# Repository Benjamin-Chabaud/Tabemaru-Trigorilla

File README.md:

# Tabemaru Control Board

## Overview
This repository contains the firmware (`tabemaru-V5-verbose.ino`) and documentation for the **Tabemaru Control Board**. The system is built around an Arduino Mega 2560 architecture (specifically using an Anycubic Trigorilla motherboard) combined with a custom PCB.

The system is designed to automate a sequence involving valves, a motor, and a heated bed, while continuously logging environmental data (temperature and humidity) to both a Serial Monitor and an SD Card in a non-blocking manner.

## Firmware Logic Explanation
The firmware is built using a non-blocking architecture, utilizing `millis()` to manage multiple tasks simultaneously without halting the processor. 

### 1. The Operational Sequence
The core logic of the machine relies on a 4-step state machine triggered by a hardware button (Button X-).
*   **Step 1 (Valve 1):** The sequence begins, the hotbed turns on, and Valve 1 opens for `1m 40s`.
*   **Step 2 (Motor):** Valve 1 closes, and the Motor runs for `5s`.
*   **Step 3 (Valve 2):** The motor stops, and Valve 2 opens for `2m 20s`.
*   **Step 4 (Wait & Hotbed):** Valve 2 closes. The system waits until the total elapsed time reaches `800s`. During this entire 800-second sequence, the heated bed actively regulates its temperature. Once 800 seconds pass, the sequence automatically terminates and resets.

*Note: All timings are defined as constants at the top of the code and can be easily modified.*

### 2. Hardware Interrupts
To ensure zero-latency responsiveness, the physical buttons do not use standard `digitalRead()` polling. Instead, they use Hardware Interrupts (`attachInterrupt`). 
*   **X- Button (Sequence Start/Stop):** Reacts instantly to start the sequence or act as an emergency stop.
*   **Z- Button (LED / SD Eject):** A short press toggles the internal LED. Holding the button for 1.5 seconds safely ejects the SD card (suspends writing) or remounts it.

### 3. SD Card & Data Storage
The system logs data in CSV format. It features a robust **Hot-Swap background task**. If the SD card is removed (or communication fails due to interference), the system will safely catch the error and attempt to re-initialize the SD card every 10 seconds. When the card is reinserted, data logging resumes automatically.

**SD Card Requirements & Formatting:**
For the SD card module to work reliably with the Arduino architecture, the following requirements MUST be met:
*   **Capacity:** 8GB is highly recommended for maximum stability (though up to 32GB SDHC is technically supported). SDXC cards (64GB+) will not work.
*   **File System:** The card MUST be formatted in **FAT32** (or FAT16). exFAT, NTFS, or APFS are not supported by the standard Arduino library.
*   **Formatting Tool & Deep Reset:** It is strongly advised to use the official SD Association's *SD Memory Card Formatter*. If the Arduino fails to initialize the card, a standard "Quick Format" is often not enough. You must select **"Overwrite Format"** (Full Format) to completely wipe the flash memory sectors and rebuild the file system from scratch.
*   **Partition Scheme:** The card's partition map MUST be **MBR (Master Boot Record)**. If the card was previously formatted on a Mac or newer OS as GPT (GUID Partition Table), the Arduino will fail to read it. To fix this, the partition table must be completely wiped (e.g., using `diskpart > clean` on Windows) before reformatting to FAT32.
*   **File Naming:** The system writes to `LOG.CSV`, strictly adhering to the legacy 8.3 filename convention.

**Data Storage Capacity & Retention:**
At the current logging rate (one entry every 2 seconds), the system generates approximately 1.2 GB of CSV data per year of continuous 24/7 operation. An 8GB SD card (the recommended maximum size for optimal compatibility) can hold data for **over 5 years** before running out of space. 

Depending on your operational needs, you can either:
*   Safely eject the SD card every few years to manually archive and delete the data.
*   Modify the logging function in the firmware to implement a rolling log (automatically deleting the oldest data when space runs out).

**Hardware & Operational Recommendations:**
*   **Logic Level Shifting:** The Arduino outputs 5V logic, but SD cards strictly require 3.3V. Ensure your SD card reader module has a built-in logic level converter chip and a 3.3V voltage regulator. Direct 5V connections will damage the SD card and cause instability.
*   **Cable Length & Interference:** The SPI protocol is highly susceptible to electromagnetic interference (EMI). Keep the SPI cables (MISO, MOSI, SCK) as short as possible and route them away from high-power cables (like the hotbed heater or motor).
*   **Flash Wear-Leveling:** Since the system writes data continuously (24/7), standard consumer SD cards may suffer from premature flash memory degradation. It is highly recommended to use a **"High Endurance"** SD card (typically used for dashcams or security cameras) designed for continuous write operations.

### 4. Environmental Monitoring & Thermostat
*   **DHT20 Sensors:** Two I2C temperature/humidity sensors are routed through a **TCA9548A Multiplexer**. They are polled every 2 seconds.
*   **Thermostat:** The system reads an NTC 100k thermistor connected to analog pin `A15` (Port T2) and uses the Steinhart-Hart equation to calculate temperature in Celsius. It maintains a target temperature of 105°C using a 1°C hysteresis.
*   **OLED Display:** A 128x32 OLED display provides real-time feedback on sequence state, actuator status, SD card health, and sensor readings.

---

## Custom PCB Analysis (KiCad)

The custom "Tabemaru control board" acts as an intermediate shield/routing board that neatly bridges the Trigorilla motherboard with the external peripherals, and also acts as a Human-Machine Interface (HMI).

### Schematic Details
1.  **I2C Multiplexer (TCA9548A):**
    *   Connectors `J1` and `J6` are designed to host a TCA9548A multiplexer breakout board. 
    *   The `sda` and `scl` lines from the Trigorilla input are fed into the multiplexer.
    *   The multiplexer outputs channels `sd1/sc1` and `sd2/sc2` to split the I2C bus, allowing two identical DHT20 sensors (which have the same hardcoded I2C address) to operate simultaneously.
2.  **DHT20 Sensor Headers:**
    *   `J2` and `J3` connect to the Top and Bottom DHT20 sensors. They receive the separated I2C channels from the multiplexer alongside VCC and GND.
3.  **Trigorilla Interconnect (`J4`):**
    *   This 6-pin connector bridges the custom PCB back to the main Trigorilla board. It carries the primary I2C bus (`sda`, `scl`), Ground, VCC, and the two button signals (`bp1`, `bp2`).
4.  **OLED Screen Header (`J5`):**
    *   This 10-pin header routes `VCC`, `GND`, `sda`, and `scl` directly to the OLED screen. Notes indicate that `sc1` and `sd1` are connected just to physically route them through the connector, though they are not utilized by the screen itself.
5.  **User Inputs (Buttons):**
    *   `SW1` and `SW2` are tactile push buttons that pull the `bp1` and `bp2` lines to Ground when pressed. These correspond to the X- and Z- endstop logic in the code.
6.  **Power Delivery & Decoupling:**
    *   Capacitors `C1`, `C2`, `C3`, `C4` are placed across the VCC and GND lines to stabilize the power delivery to the sensors and ICs, preventing voltage drops and filtering out electrical noise.

### PCB Layout Notes
*   The PCB is a two-layer board (Top Copper in Red, Bottom Copper in Blue). Both sides are identical and interconnected so that the connectors can be mounted on either side depending on the final position of the board inside the composter. Although this makes the routing technically less optimized (for instance, a VCC line making a half-loop is not ideal), it provides necessary mechanical flexibility for prototyping.
*   Thick traces are used for the main VCC and GND rails to ensure stable current delivery, while thinner traces are used for data lines (`sda`, `scl`).
*   The design elegantly centralizes all messy external wiring (buttons, screen, sensors) into a single, clean interface board that connects directly to the Trigorilla via the `J4` header.

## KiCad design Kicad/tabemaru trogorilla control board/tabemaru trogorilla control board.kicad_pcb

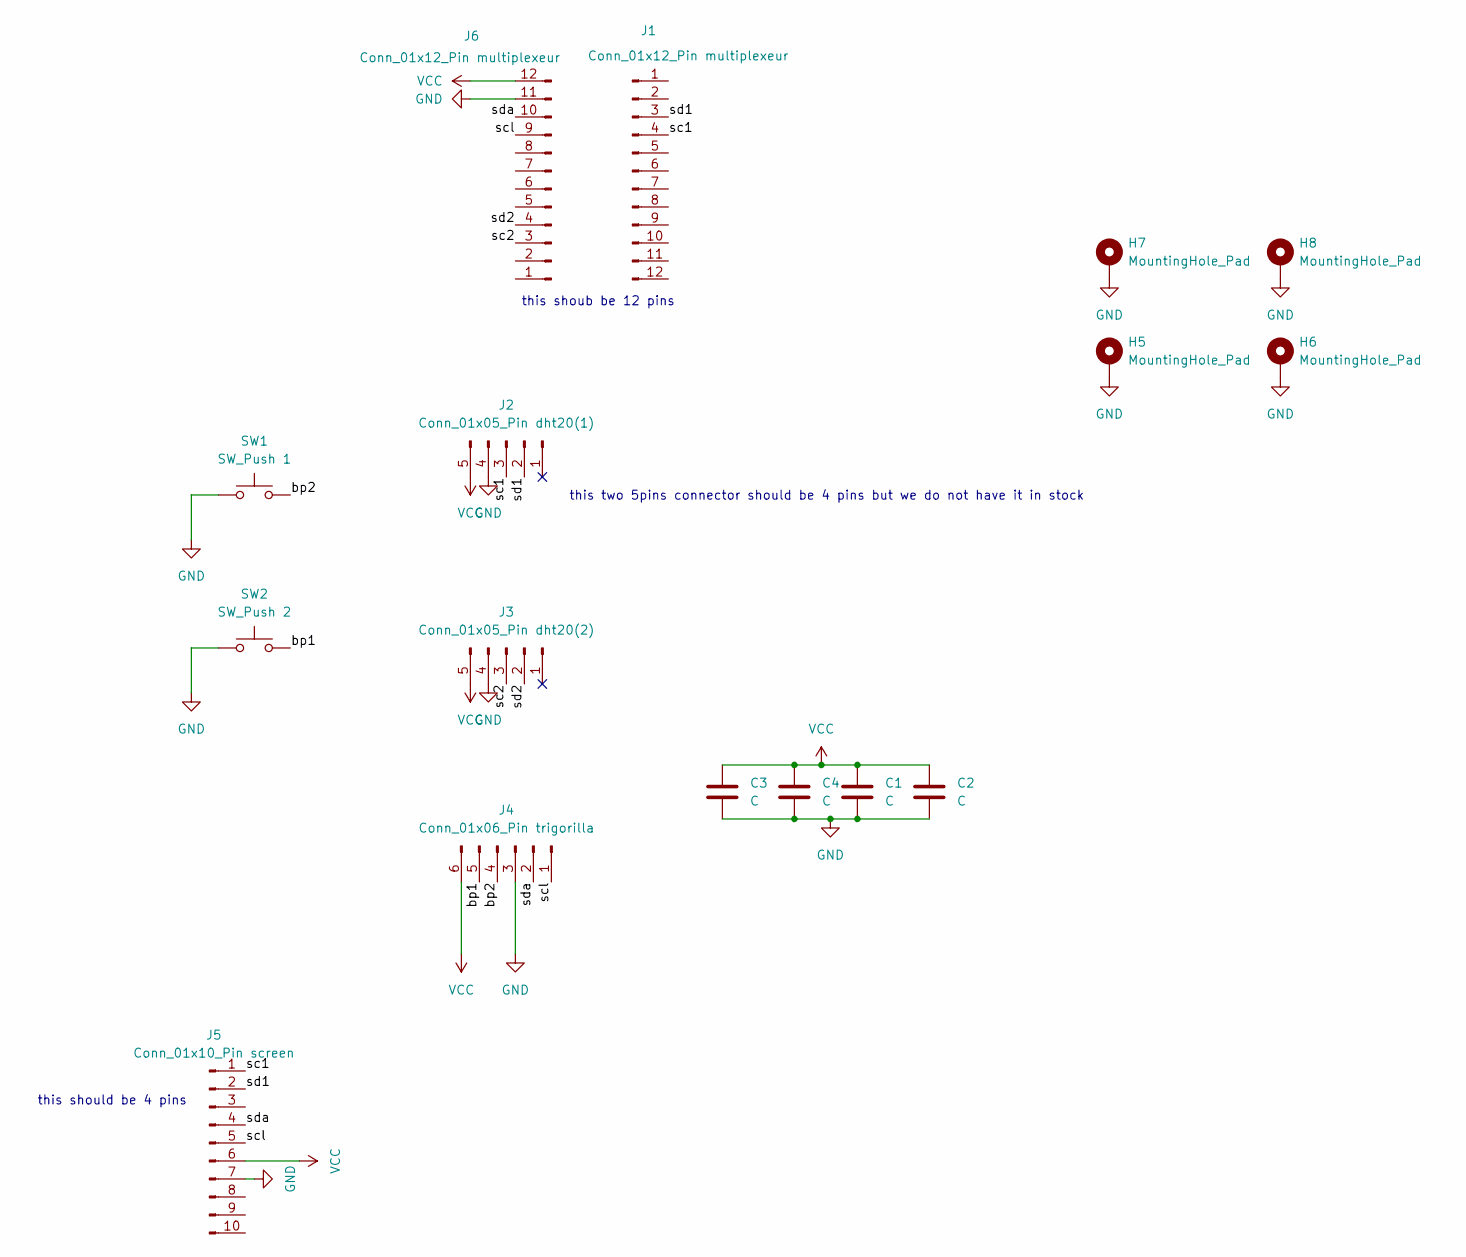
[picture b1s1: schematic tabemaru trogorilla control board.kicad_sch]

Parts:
C1, C2, C3, C4: C; PinHeader_1x02_P2.54mm_Vertical
H5, H6, H7, H8: MountingHole_Pad; MountingHole_3.5mm_Pad
J1, J6: Conn_01x12_Pin multiplexeur; PinHeader_1x12_P2.54mm_Vertical
J2: Conn_01x05_Pin dht20(1); JST_XH_B5B-XH-A_1x05_P2.50mm_Vertical
J3: Conn_01x05_Pin dht20(2); JST_XH_B5B-XH-A_1x05_P2.50mm_Vertical
J4: Conn_01x06_Pin trigorilla; JST_XH_B6B-XH-A_1x06_P2.50mm_Vertical
J5: Conn_01x10_Pin screen; PinHeader_1x10_P2.54mm_Vertical
SW1: SW_Push 1; SW_PUSH_6mm_H4.3mm
SW2: SW_Push 2; SW_PUSH_6mm_H4.3mm

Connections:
/bp1: J4.5, SW2.2
/bp2: J4.4, SW1.2
/sc1: J1.4, J2.3, J5.1
/sc2: J3.3, J6.3
/scl: J4.1, J5.5, J6.9
/sd1: J1.3, J2.2, J5.2
/sd2: J3.2, J6.4
/sda: J4.2, J5.4, J6.10
GND: C1.2, C2.2, C3.2, C4.2, H5.1 (1_1), H6.1 (1_1), H7.1 (1_1), H8.1 (1_1), J2.4, J3.4, J4.3, J5.7, J6.11, SW1.1, SW2.1
VCC: C1.1, C2.1, C3.1, C4.1, J2.5, J3.5, J4.6, J5.6, J6.12

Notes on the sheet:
this should be 4 pins
this shoub be 12 pins
this two 5pins connector should be 4 pins but we do not have it in stock

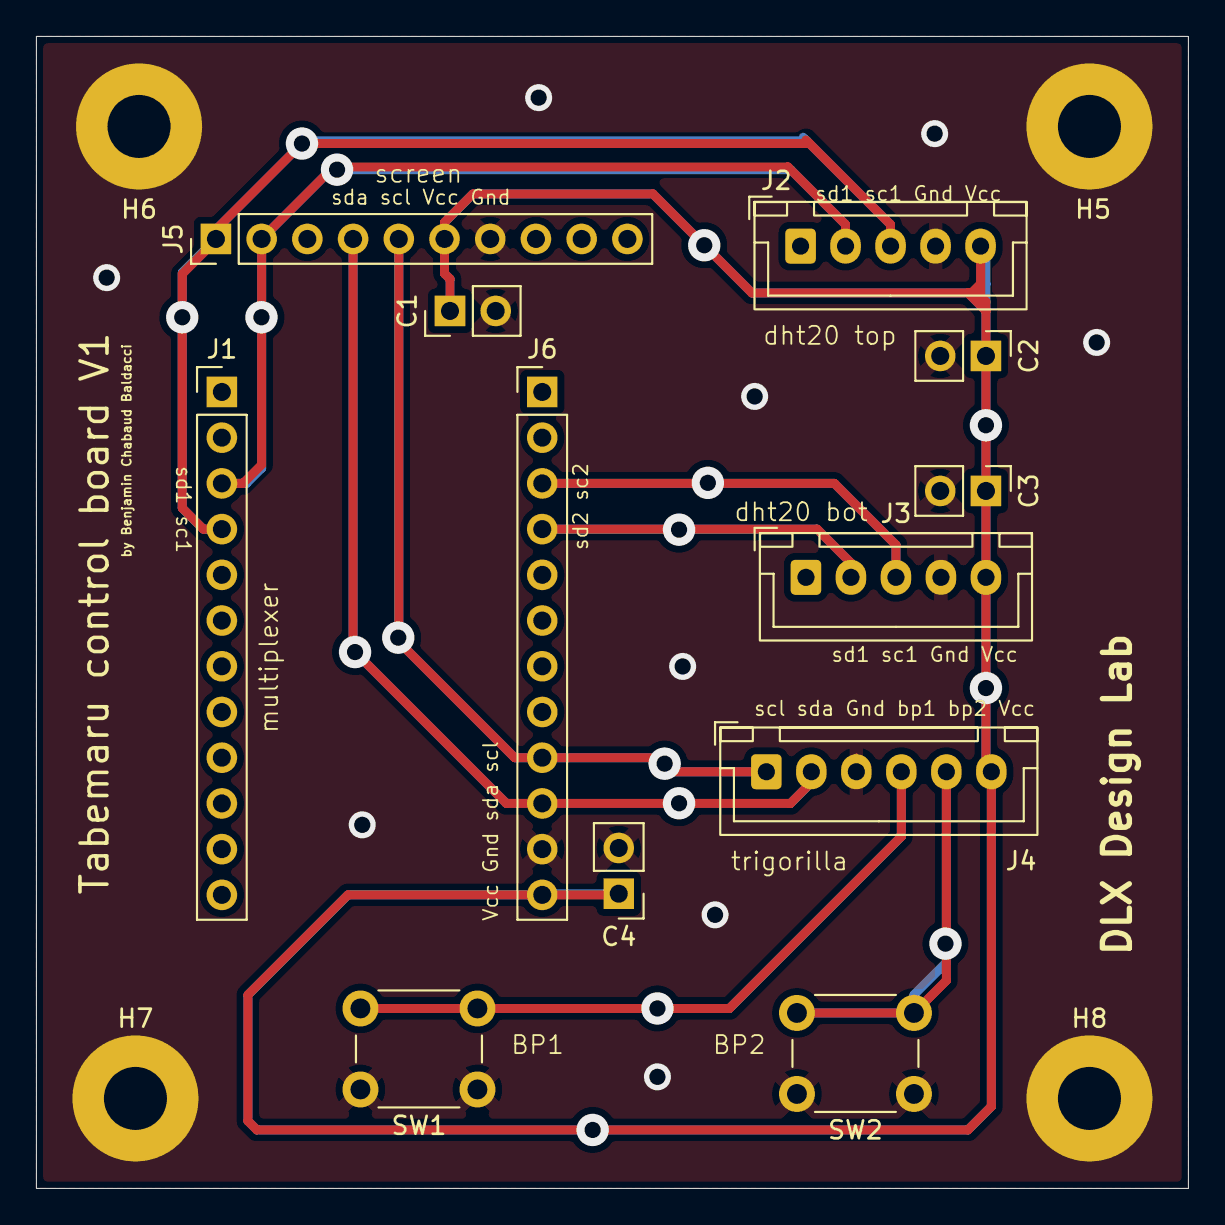
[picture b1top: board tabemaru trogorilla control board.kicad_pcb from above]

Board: 2 copper layers, 64.0 x 64.0 mm, 16 parts (0 on the bottom side), 10 nets.

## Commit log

2026-06-02 1st commit
2026-06-02 readme update
